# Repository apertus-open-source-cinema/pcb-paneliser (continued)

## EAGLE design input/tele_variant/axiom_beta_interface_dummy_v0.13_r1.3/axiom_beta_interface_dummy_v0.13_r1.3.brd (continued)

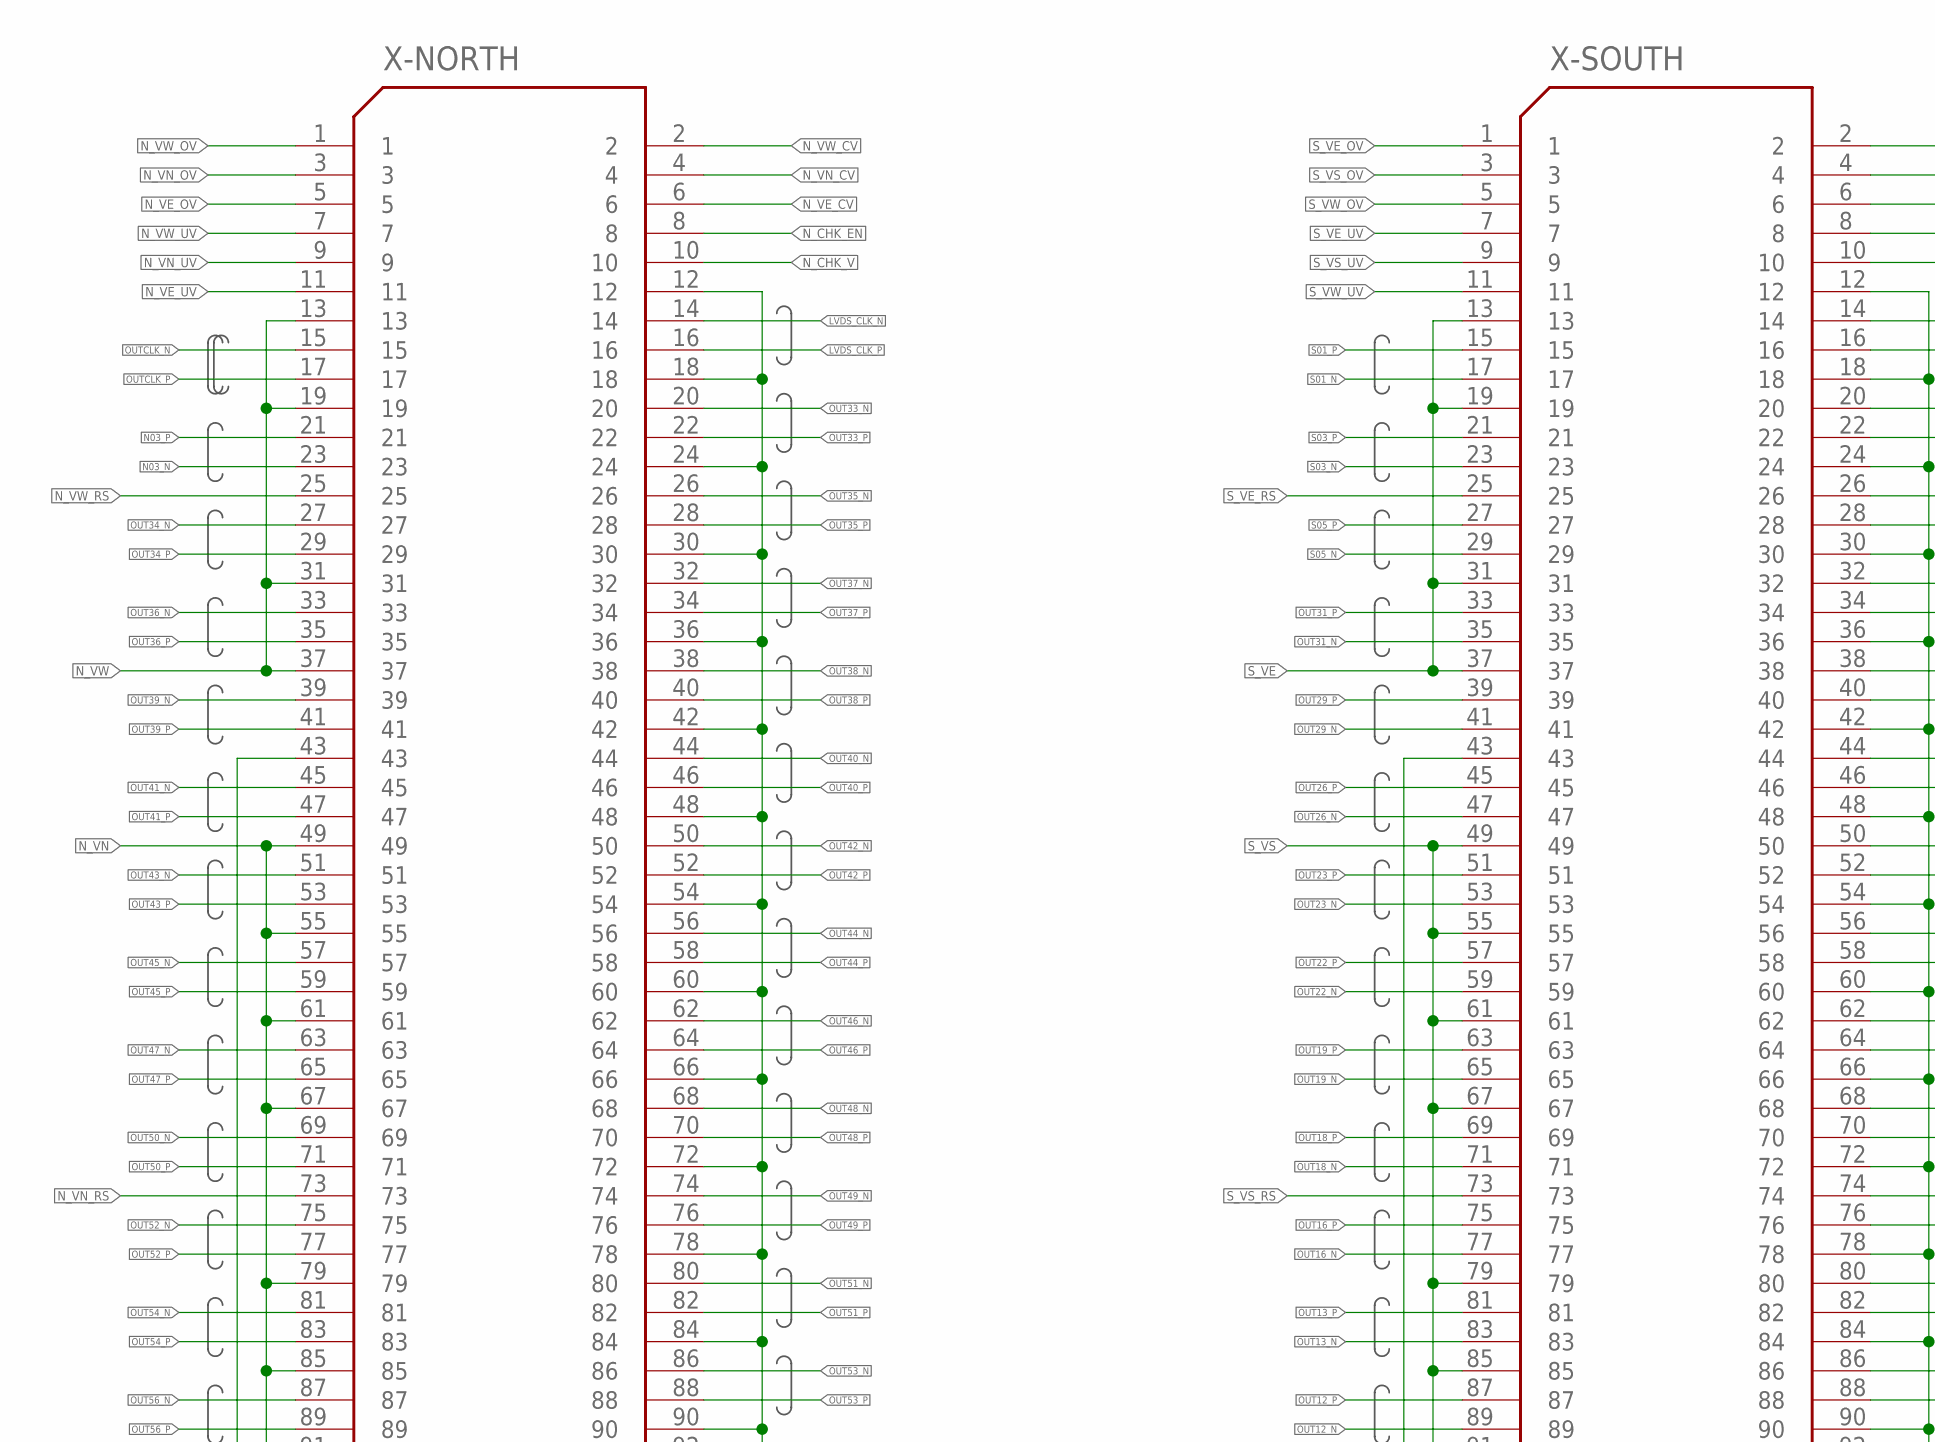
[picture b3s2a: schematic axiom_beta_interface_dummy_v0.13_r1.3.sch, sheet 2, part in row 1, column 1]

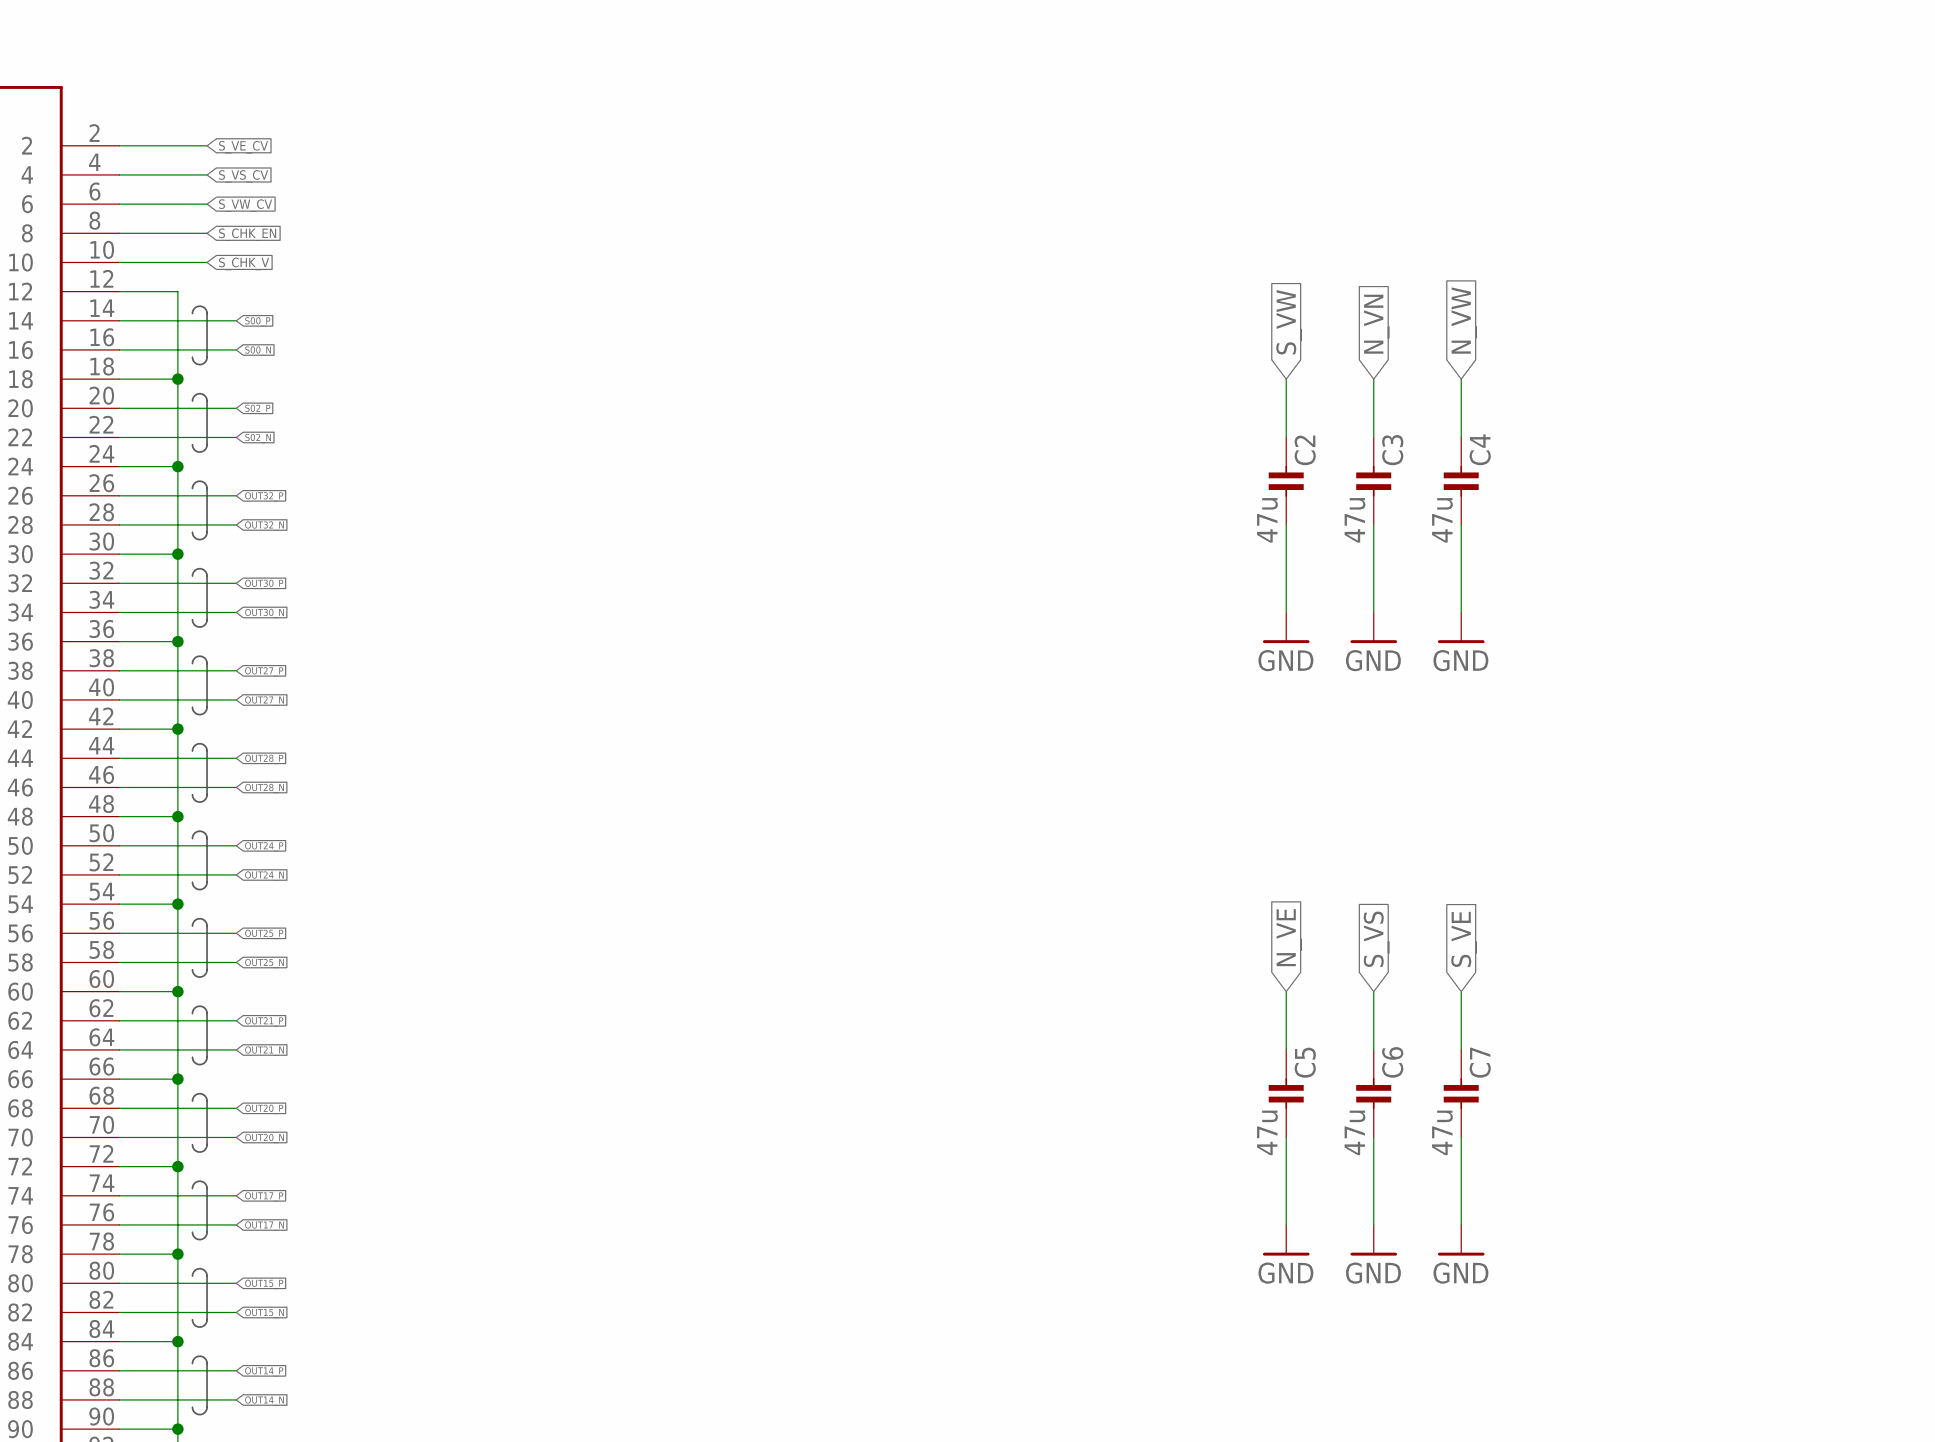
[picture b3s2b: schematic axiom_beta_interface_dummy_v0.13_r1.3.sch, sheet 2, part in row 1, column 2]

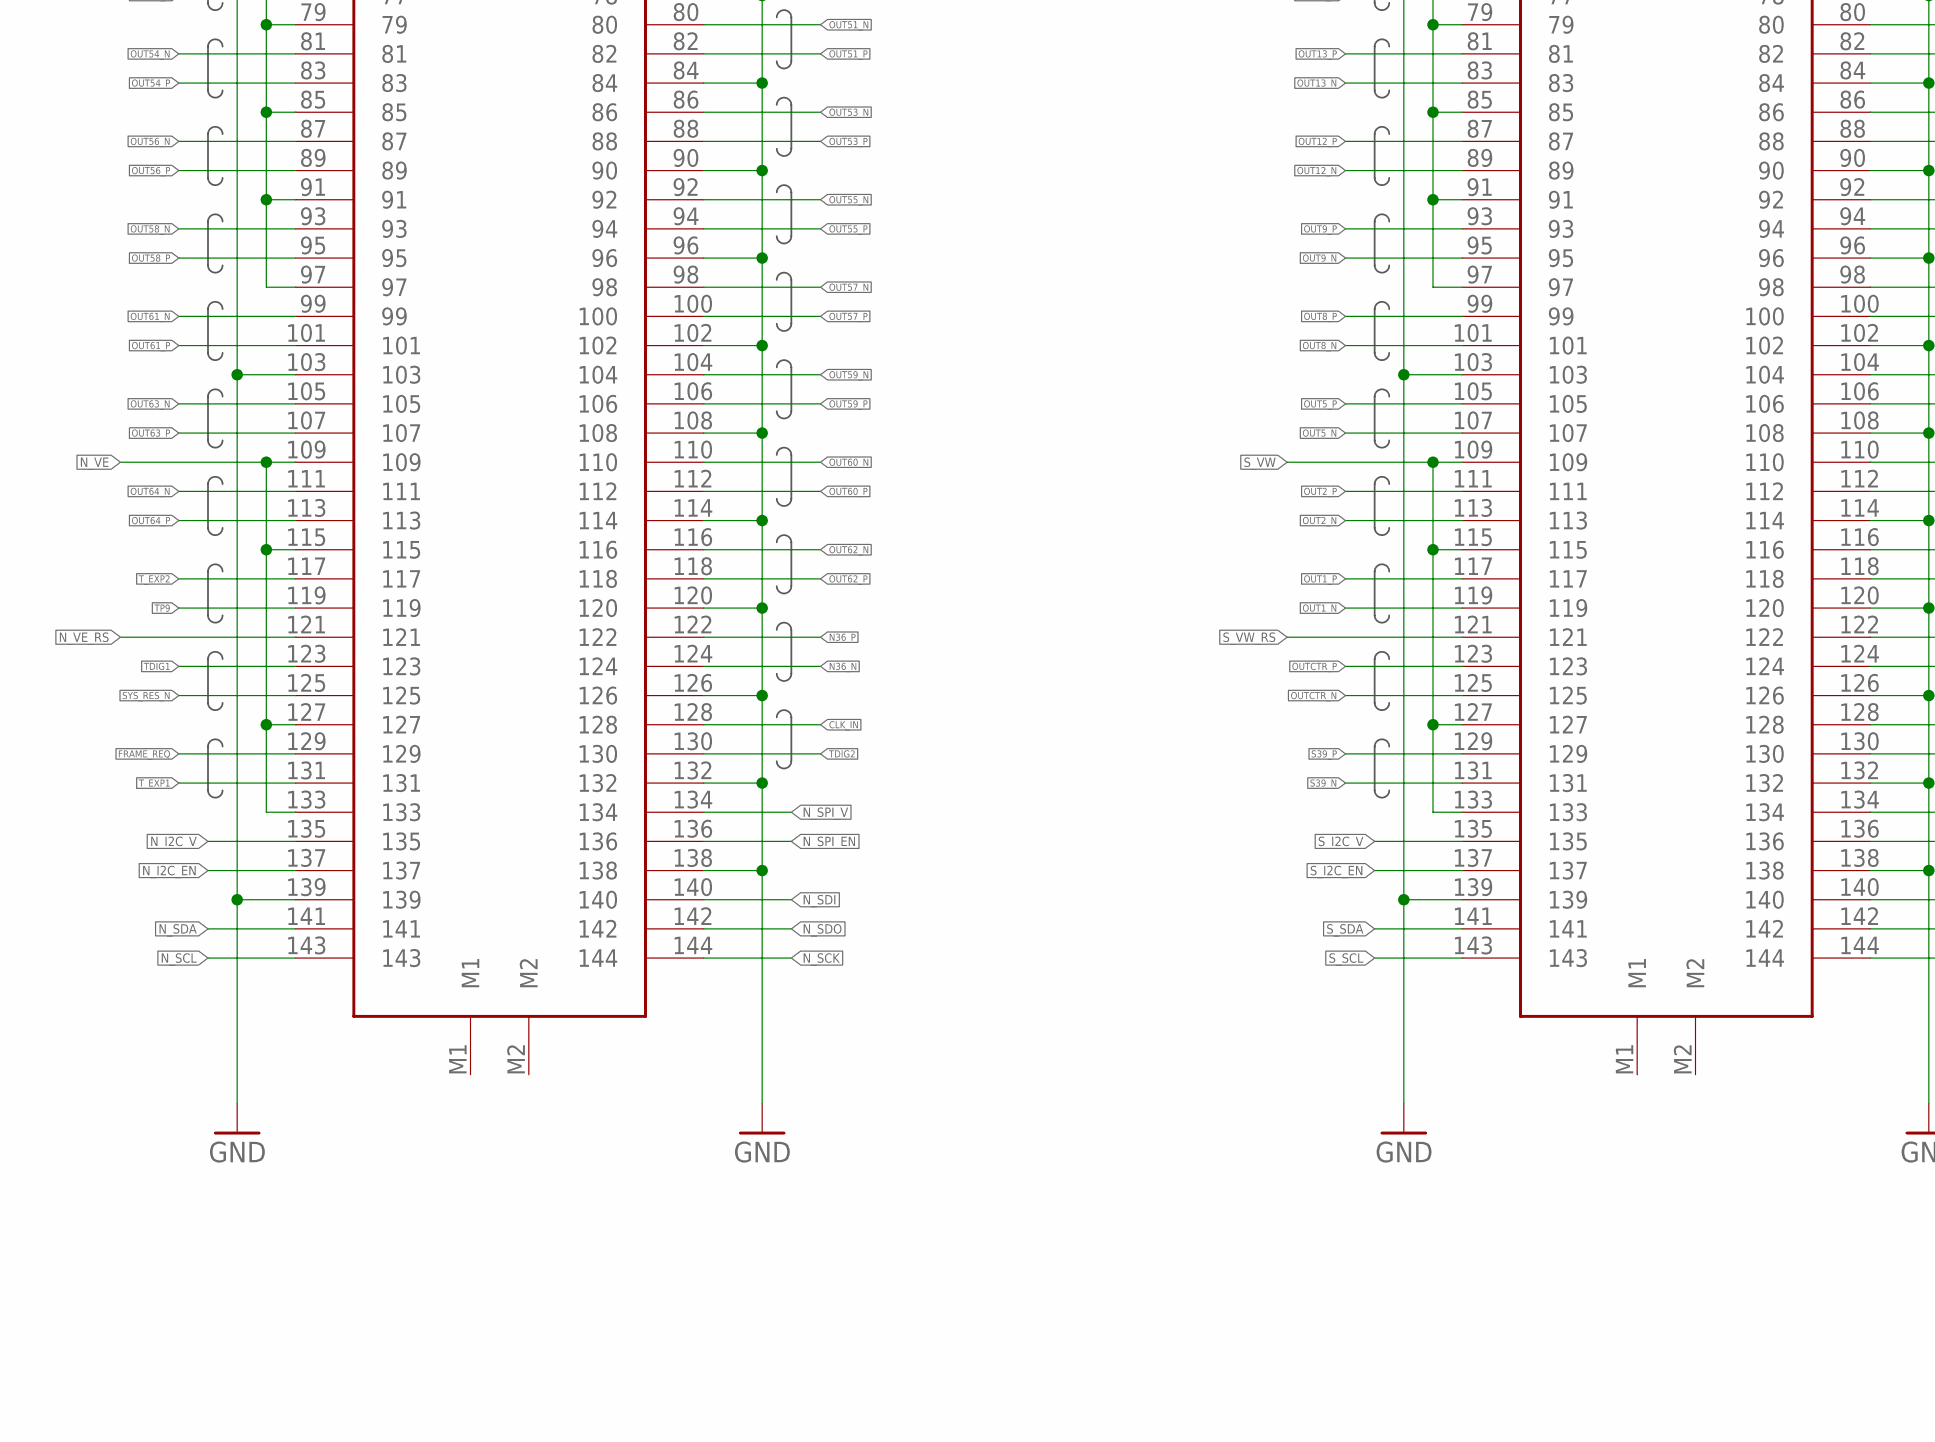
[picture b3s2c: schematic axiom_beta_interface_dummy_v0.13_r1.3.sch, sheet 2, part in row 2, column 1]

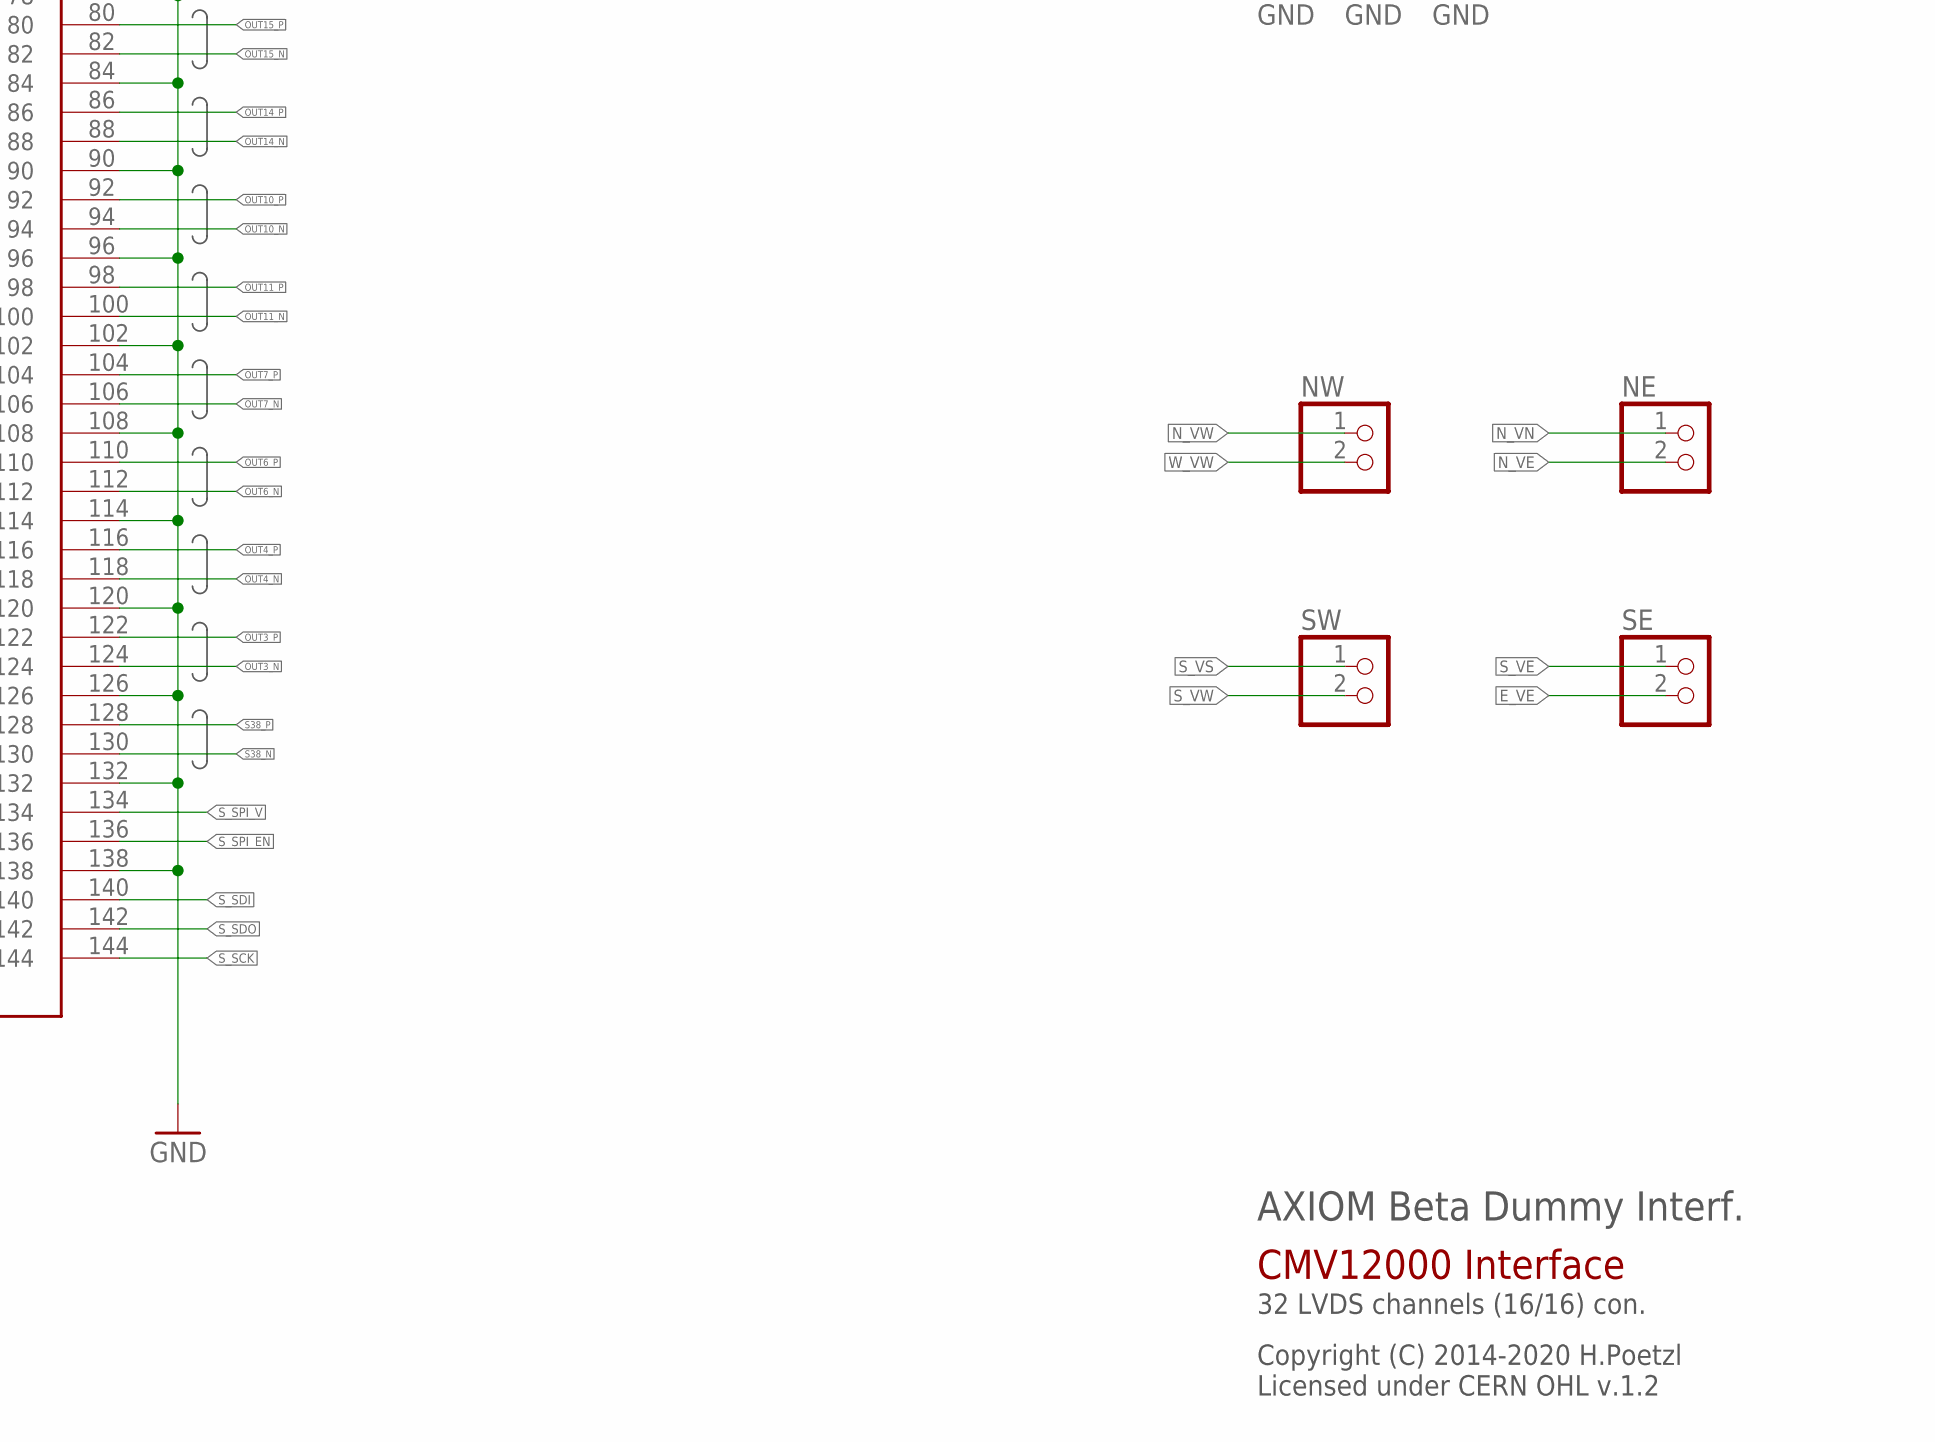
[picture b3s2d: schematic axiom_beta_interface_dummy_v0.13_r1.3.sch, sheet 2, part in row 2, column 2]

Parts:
C2, C3, C4, C5, C6, C7: 47u; 0805-B
NE: PINHD-1X02_2.54; 1X02
NW: PINHD-1X02_2.54; 1X02
SE: PINHD-1X02_2.54; 1X02
SW: PINHD-1X02_2.54; 1X02
X-NORTH: FX10-144S; FX10A-144S
X-SOUTH: FX10-144S; FX10A-144S

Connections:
CLK_IN: X-NORTH.128; also elsewhere on the board
E_VE: SE.2; also elsewhere on the board
FRAME_REQ: X-NORTH.129; also elsewhere on the board
GND: C2.2, C3.2, C4.2, C5.2, C6.2, C7.2, X-NORTH.12, X-NORTH.18, X-NORTH.24, X-NORTH.30, X-NORTH.36, X-NORTH.42, X-NORTH.43, X-NORTH.48, X-NORTH.54, X-NORTH.60, X-NORTH.66, X-NORTH.72, X-NORTH.78, X-NORTH.84, X-NORTH.90, X-NORTH.96, X-NORTH.102, X-NORTH.103, X-NORTH.108, X-NORTH.114, X-NORTH.120, X-NORTH.126, X-NORTH.132, X-NORTH.138, X-NORTH.139, X-SOUTH.12, X-SOUTH.18, X-SOUTH.24, X-SOUTH.30, X-SOUTH.36, X-SOUTH.42, X-SOUTH.43, X-SOUTH.48, X-SOUTH.54, X-SOUTH.60, X-SOUTH.66, X-SOUTH.72, X-SOUTH.78, X-SOUTH.84, X-SOUTH.90, X-SOUTH.96, X-SOUTH.102, X-SOUTH.103, X-SOUTH.108, X-SOUTH.114, X-SOUTH.120, X-SOUTH.126, X-SOUTH.132, X-SOUTH.138, X-SOUTH.139; also elsewhere on the board
LVDS_CLK_N: X-NORTH.14; also elsewhere on the board
LVDS_CLK_P: X-NORTH.16; also elsewhere on the board
N03_N: X-NORTH.23
N03_P: X-NORTH.21
N36_N: X-NORTH.124
N36_P: X-NORTH.122
N_CHK_EN: X-NORTH.8; also elsewhere on the board
N_CHK_V: X-NORTH.10; also elsewhere on the board
N_I2C_EN: X-NORTH.137; also elsewhere on the board
N_I2C_V: X-NORTH.135; also elsewhere on the board
N_SCK: X-NORTH.144; also elsewhere on the board
N_SCL: X-NORTH.143; also elsewhere on the board
N_SDA: X-NORTH.141; also elsewhere on the board
N_SDI: X-NORTH.140; also elsewhere on the board
N_SDO: X-NORTH.142; also elsewhere on the board
N_SPI_EN: X-NORTH.136; also elsewhere on the board
N_SPI_V: X-NORTH.134; also elsewhere on the board
N_VE: C5.1, NE.2, X-NORTH.109, X-NORTH.115, X-NORTH.127, X-NORTH.133
N_VE_CV: X-NORTH.6; also elsewhere on the board
N_VE_OV: X-NORTH.5; also elsewhere on the board
N_VE_RS: X-NORTH.121; also elsewhere on the board
N_VE_UV: X-NORTH.11; also elsewhere on the board
N_VN: C3.1, NE.1, X-NORTH.49, X-NORTH.55, X-NORTH.61, X-NORTH.67, X-NORTH.79, X-NORTH.85, X-NORTH.91, X-NORTH.97
N_VN_CV: X-NORTH.4; also elsewhere on the board
N_VN_OV: X-NORTH.3; also elsewhere on the board
N_VN_RS: X-NORTH.73; also elsewhere on the board
N_VN_UV: X-NORTH.9; also elsewhere on the board
N_VW: C4.1, NW.1, X-NORTH.13, X-NORTH.19, X-NORTH.31, X-NORTH.37
N_VW_CV: X-NORTH.2; also elsewhere on the board
N_VW_OV: X-NORTH.1; also elsewhere on the board
N_VW_RS: X-NORTH.25; also elsewhere on the board
N_VW_UV: X-NORTH.7; also elsewhere on the board
OUT1_N: X-SOUTH.119; also elsewhere on the board
OUT1_P: X-SOUTH.117; also elsewhere on the board
OUT2_N: X-SOUTH.113
OUT2_P: X-SOUTH.111
OUT3_N: X-SOUTH.124; also elsewhere on the board
OUT3_P: X-SOUTH.122; also elsewhere on the board
OUT4_N: X-SOUTH.118
OUT4_P: X-SOUTH.116
OUT5_N: X-SOUTH.107; also elsewhere on the board
OUT5_P: X-SOUTH.105; also elsewhere on the board
OUT6_N: X-SOUTH.112
OUT6_P: X-SOUTH.110
OUT7_N: X-SOUTH.106; also elsewhere on the board
OUT7_P: X-SOUTH.104; also elsewhere on the board
OUT8_N: X-SOUTH.101
OUT8_P: X-SOUTH.99
OUT9_N: X-SOUTH.95; also elsewhere on the board
OUT9_P: X-SOUTH.93; also elsewhere on the board
OUT10_N: X-SOUTH.94
OUT10_P: X-SOUTH.92
OUT11_N: X-SOUTH.100; also elsewhere on the board
OUT11_P: X-SOUTH.98; also elsewhere on the board
OUT12_N: X-SOUTH.89
OUT12_P: X-SOUTH.87
OUT13_N: X-SOUTH.83; also elsewhere on the board
OUT13_P: X-SOUTH.81; also elsewhere on the board
OUT14_N: X-SOUTH.88
OUT14_P: X-SOUTH.86
OUT15_N: X-SOUTH.82; also elsewhere on the board
OUT15_P: X-SOUTH.80; also elsewhere on the board
OUT16_N: X-SOUTH.77
OUT16_P: X-SOUTH.75
OUT17_N: X-SOUTH.76; also elsewhere on the board
OUT17_P: X-SOUTH.74; also elsewhere on the board
OUT18_N: X-SOUTH.71
OUT18_P: X-SOUTH.69
OUT19_N: X-SOUTH.65; also elsewhere on the board
OUT19_P: X-SOUTH.63; also elsewhere on the board
OUT20_N: X-SOUTH.70
OUT20_P: X-SOUTH.68
OUT21_N: X-SOUTH.64; also elsewhere on the board
OUT21_P: X-SOUTH.62; also elsewhere on the board
OUT22_N: X-SOUTH.59
OUT22_P: X-SOUTH.57
OUT23_N: X-SOUTH.53; also elsewhere on the board
OUT23_P: X-SOUTH.51; also elsewhere on the board
OUT24_N: X-SOUTH.52
OUT24_P: X-SOUTH.50
OUT25_N: X-SOUTH.58; also elsewhere on the board
OUT25_P: X-SOUTH.56; also elsewhere on the board
OUT26_N: X-SOUTH.47
OUT26_P: X-SOUTH.45
OUT27_N: X-SOUTH.40; also elsewhere on the board
OUT27_P: X-SOUTH.38; also elsewhere on the board
OUT28_N: X-SOUTH.46
OUT28_P: X-SOUTH.44
OUT29_N: X-SOUTH.41; also elsewhere on the board
OUT29_P: X-SOUTH.39; also elsewhere on the board
OUT30_N: X-SOUTH.34
OUT30_P: X-SOUTH.32
OUT31_N: X-SOUTH.35; also elsewhere on the board
OUT31_P: X-SOUTH.33; also elsewhere on the board
OUT32_N: X-SOUTH.28
OUT32_P: X-SOUTH.26
OUT33_N: X-NORTH.20; also elsewhere on the board
OUT33_P: X-NORTH.22; also elsewhere on the board
OUT34_N: X-NORTH.27
OUT34_P: X-NORTH.29
OUT35_N: X-NORTH.26; also elsewhere on the board
OUT35_P: X-NORTH.28; also elsewhere on the board
OUT36_N: X-NORTH.33
OUT36_P: X-NORTH.35
OUT37_N: X-NORTH.32; also elsewhere on the board
OUT37_P: X-NORTH.34; also elsewhere on the board
OUT38_N: X-NORTH.38
OUT38_P: X-NORTH.40
OUT39_N: X-NORTH.39; also elsewhere on the board
OUT39_P: X-NORTH.41; also elsewhere on the board
OUT40_N: X-NORTH.44
OUT40_P: X-NORTH.46
OUT41_N: X-NORTH.45; also elsewhere on the board
OUT41_P: X-NORTH.47; also elsewhere on the board
OUT42_N: X-NORTH.50
OUT42_P: X-NORTH.52
OUT43_N: X-NORTH.51; also elsewhere on the board
OUT43_P: X-NORTH.53; also elsewhere on the board
OUT44_N: X-NORTH.56
OUT44_P: X-NORTH.58
OUT45_N: X-NORTH.57; also elsewhere on the board
OUT45_P: X-NORTH.59; also elsewhere on the board
OUT46_N: X-NORTH.62
OUT46_P: X-NORTH.64
OUT47_N: X-NORTH.63; also elsewhere on the board
OUT47_P: X-NORTH.65; also elsewhere on the board
OUT48_N: X-NORTH.68
OUT48_P: X-NORTH.70
OUT49_N: X-NORTH.74; also elsewhere on the board
OUT49_P: X-NORTH.76; also elsewhere on the board
OUT50_N: X-NORTH.69
OUT50_P: X-NORTH.71
OUT51_N: X-NORTH.80; also elsewhere on the board
OUT51_P: X-NORTH.82; also elsewhere on the board
OUT52_N: X-NORTH.75
OUT52_P: X-NORTH.77
OUT53_N: X-NORTH.86; also elsewhere on the board
OUT53_P: X-NORTH.88; also elsewhere on the board
OUT54_N: X-NORTH.81
OUT54_P: X-NORTH.83
OUT55_N: X-NORTH.92; also elsewhere on the board
OUT55_P: X-NORTH.94; also elsewhere on the board
OUT56_N: X-NORTH.87
OUT56_P: X-NORTH.89
OUT57_N: X-NORTH.98; also elsewhere on the board
OUT57_P: X-NORTH.100; also elsewhere on the board
OUT58_N: X-NORTH.93
OUT58_P: X-NORTH.95
OUT59_N: X-NORTH.104; also elsewhere on the board
OUT59_P: X-NORTH.106; also elsewhere on the board
OUT60_N: X-NORTH.110
OUT60_P: X-NORTH.112
OUT61_N: X-NORTH.99; also elsewhere on the board
OUT61_P: X-NORTH.101; also elsewhere on the board
OUT62_N: X-NORTH.116
OUT62_P: X-NORTH.118
OUT63_N: X-NORTH.105; also elsewhere on the board
OUT63_P: X-NORTH.107; also elsewhere on the board
OUT64_N: X-NORTH.111
OUT64_P: X-NORTH.113
OUTCLK_N: X-NORTH.15; also elsewhere on the board
OUTCLK_P: X-NORTH.17; also elsewhere on the board
OUTCTR_N: X-SOUTH.125; also elsewhere on the board
OUTCTR_P: X-SOUTH.123; also elsewhere on the board
S00_N: X-SOUTH.16
S00_P: X-SOUTH.14
S01_N: X-SOUTH.17
S01_P: X-SOUTH.15
S02_N: X-SOUTH.22
S02_P: X-SOUTH.20
S03_N: X-SOUTH.23
S03_P: X-SOUTH.21
S05_N: X-SOUTH.29
S05_P: X-SOUTH.27
S38_N: X-SOUTH.130
S38_P: X-SOUTH.128
S39_N: X-SOUTH.131
S39_P: X-SOUTH.129
SYS_RES_N: X-NORTH.125; also elsewhere on the board
S_CHK_EN: X-SOUTH.8; also elsewhere on the board
S_CHK_V: X-SOUTH.10; also elsewhere on the board
S_I2C_EN: X-SOUTH.137; also elsewhere on the board
S_I2C_V: X-SOUTH.135; also elsewhere on the board
S_SCK: X-SOUTH.144; also elsewhere on the board
S_SCL: X-SOUTH.143; also elsewhere on the board
S_SDA: X-SOUTH.141; also elsewhere on the board
S_SDI: X-SOUTH.140; also elsewhere on the board
S_SDO: X-SOUTH.142; also elsewhere on the board
S_SPI_EN: X-SOUTH.136; also elsewhere on the board
S_SPI_V: X-SOUTH.134; also elsewhere on the board
S_VE: C7.1, SE.1, X-SOUTH.13, X-SOUTH.19, X-SOUTH.31, X-SOUTH.37
S_VE_CV: X-SOUTH.2; also elsewhere on the board
S_VE_OV: X-SOUTH.1; also elsewhere on the board
S_VE_RS: X-SOUTH.25; also elsewhere on the board
S_VE_UV: X-SOUTH.7; also elsewhere on the board
S_VS: C6.1, SW.1, X-SOUTH.49, X-SOUTH.55, X-SOUTH.61, X-SOUTH.67, X-SOUTH.79, X-SOUTH.85, X-SOUTH.91, X-SOUTH.97
S_VS_CV: X-SOUTH.4; also elsewhere on the board
S_VS_OV: X-SOUTH.3; also elsewhere on the board
S_VS_RS: X-SOUTH.73; also elsewhere on the board
S_VS_UV: X-SOUTH.9; also elsewhere on the board
S_VW: C2.1, SW.2, X-SOUTH.109, X-SOUTH.115, X-SOUTH.127, X-SOUTH.133
S_VW_CV: X-SOUTH.6; also elsewhere on the board
S_VW_OV: X-SOUTH.5; also elsewhere on the board
S_VW_RS: X-SOUTH.121; also elsewhere on the board
S_VW_UV: X-SOUTH.11; also elsewhere on the board
TDIG1: X-NORTH.123; also elsewhere on the board
TDIG2: X-NORTH.130
TP9: X-NORTH.119
T_EXP1: X-NORTH.131; also elsewhere on the board
T_EXP2: X-NORTH.117; also elsewhere on the board
W_VW: NW.2; also elsewhere on the board

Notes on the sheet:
AXIOM Beta Dummy Interf.
Copyright (C) 2014-2020 H.Poetzl Licensed under CERN OHL v.1.2
CMV12000 Interface
32 LVDS channels (16/16) con.

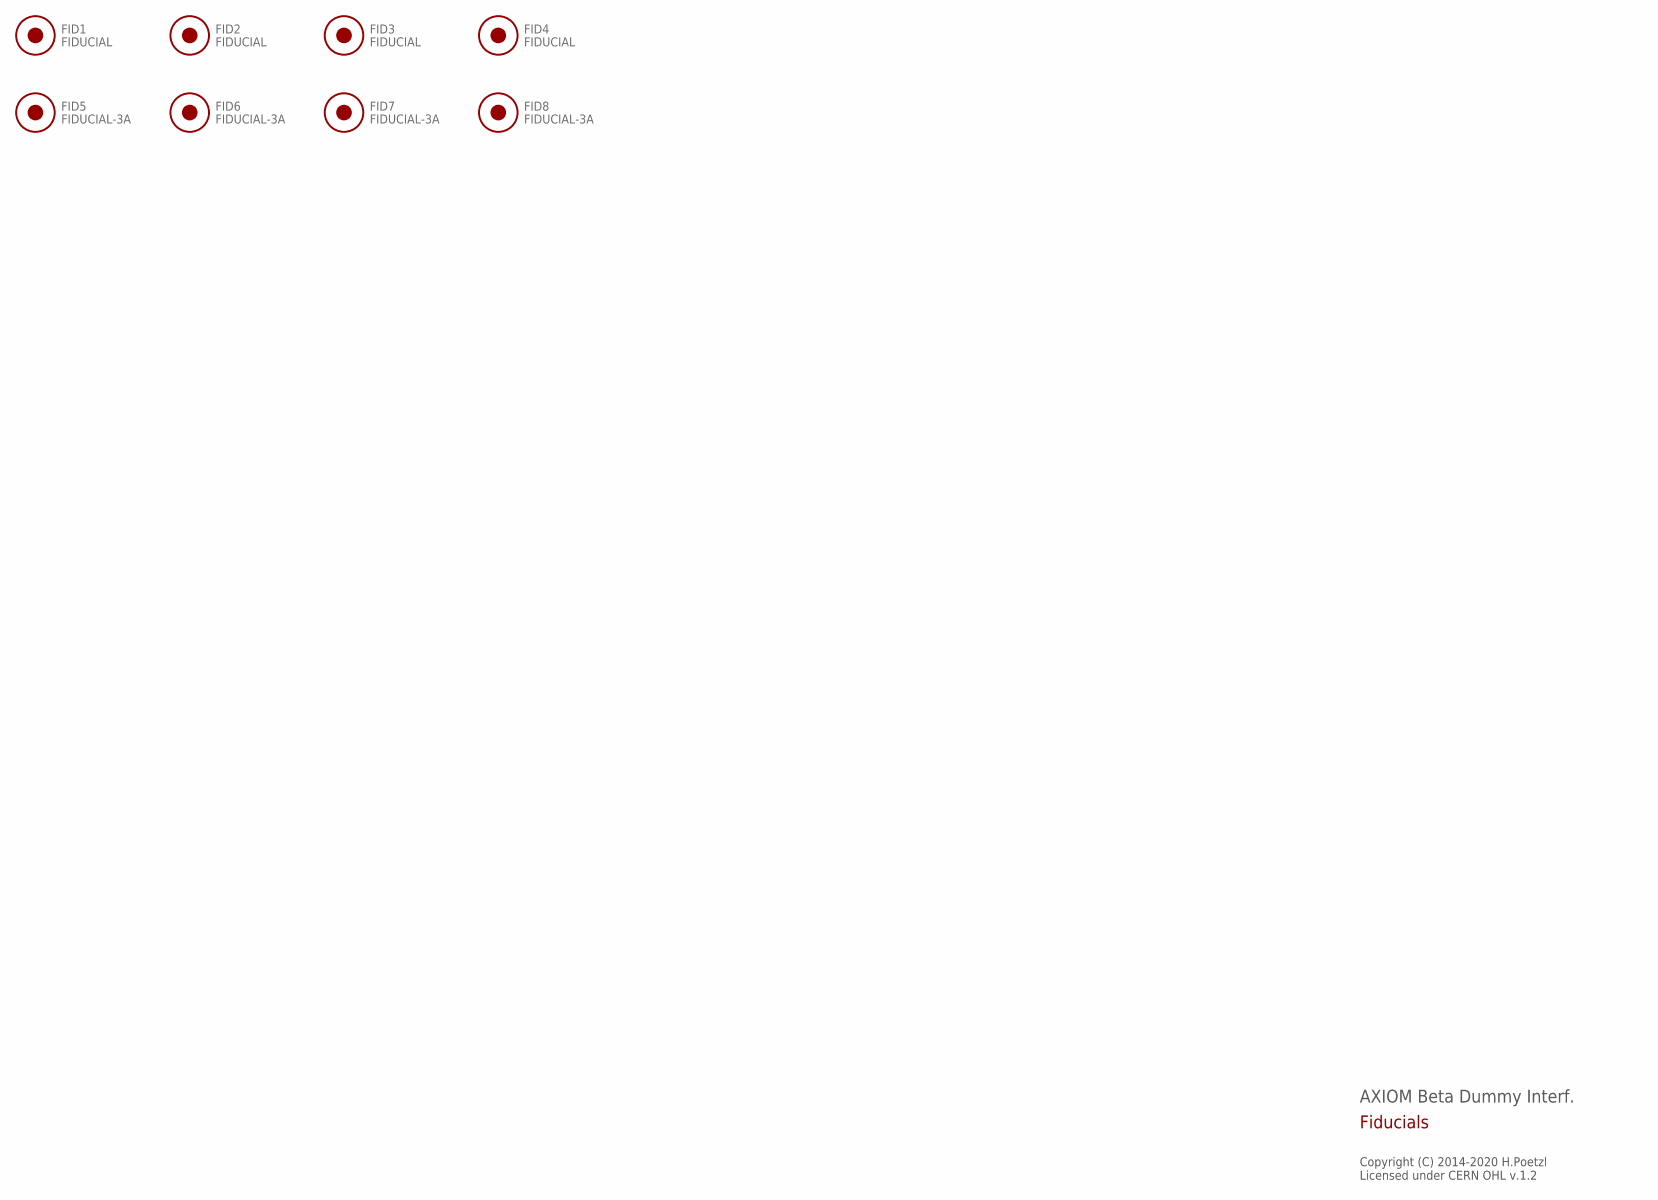
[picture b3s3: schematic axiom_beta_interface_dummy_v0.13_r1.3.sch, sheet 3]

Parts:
FID1, FID2, FID3, FID4: FIDUCIAL; FID_ARROW
FID5, FID6, FID7, FID8: FIDUCIAL-3A; FID_3ARROW

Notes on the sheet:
AXIOM Beta Dummy Interf.
Copyright (C) 2014-2020 H.Poetzl Licensed under CERN OHL v.1.2
Fiducials

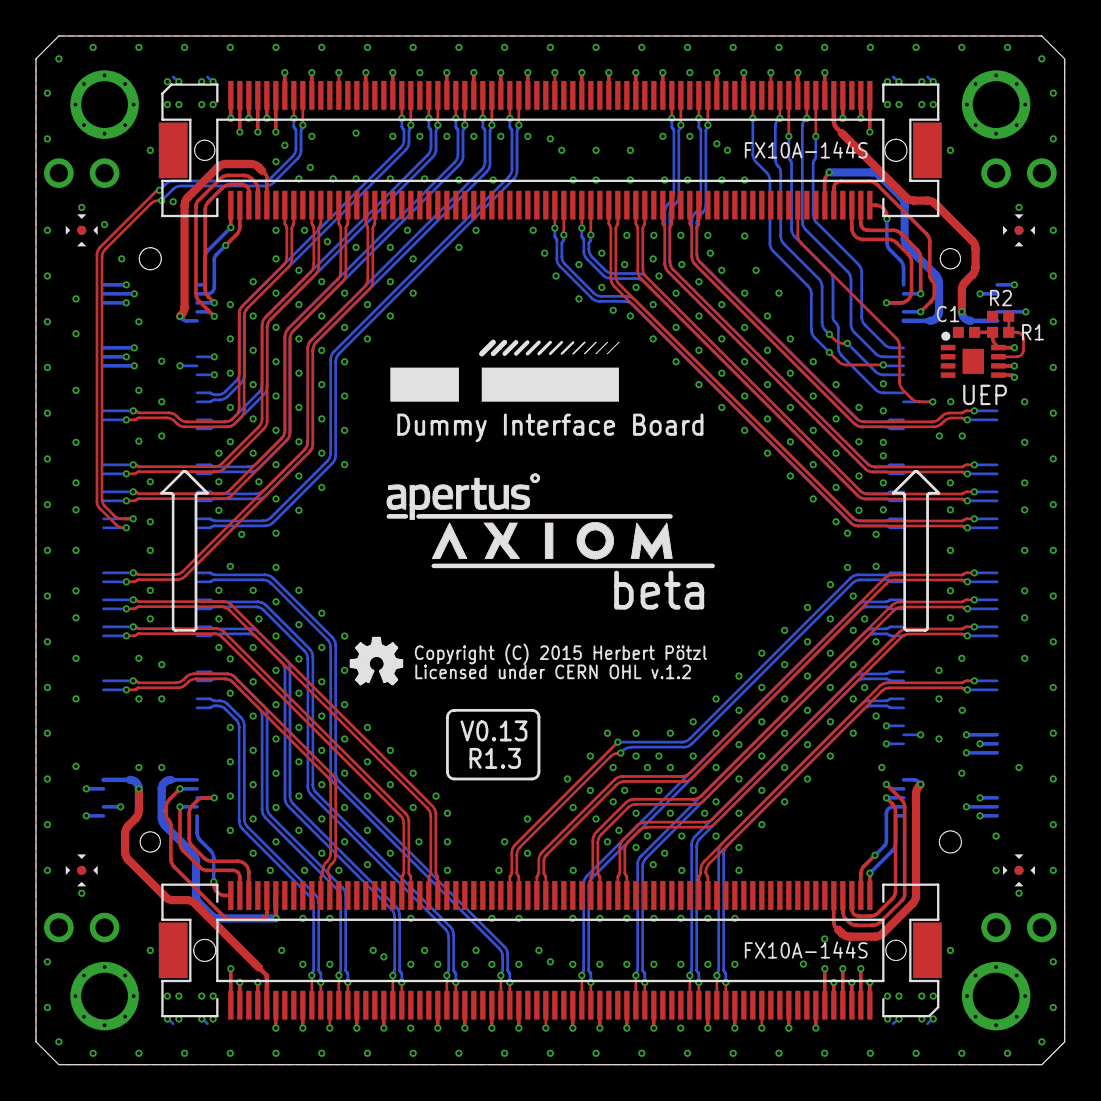
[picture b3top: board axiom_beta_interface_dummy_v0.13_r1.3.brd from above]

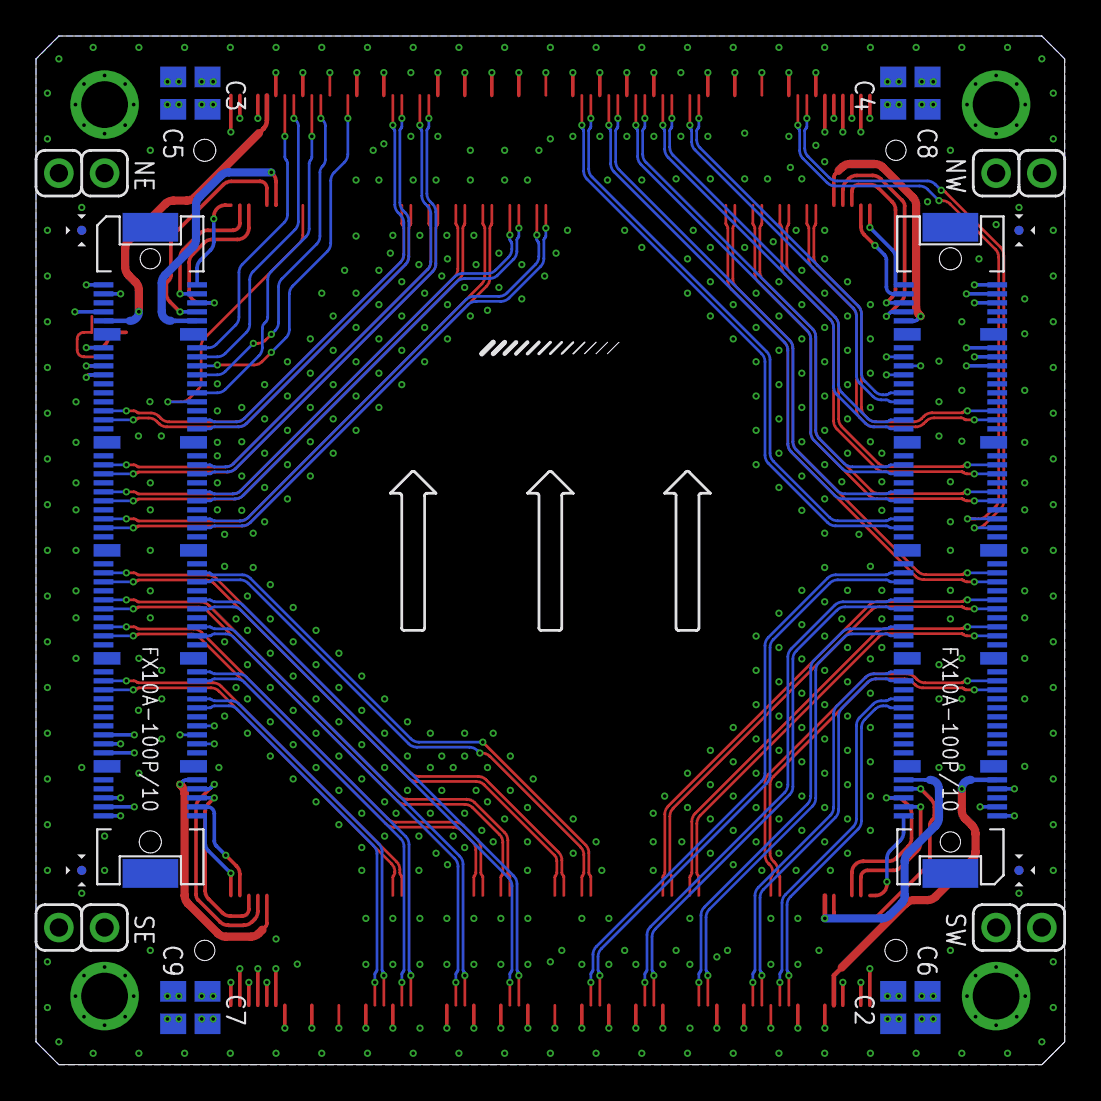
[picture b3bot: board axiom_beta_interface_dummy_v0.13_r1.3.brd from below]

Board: 4 copper layers, 57.1 x 57.1 mm, 33 parts (18 on the bottom side), 135 nets.

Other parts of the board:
LOGO1: OSHW_LOGO_FILLX0100-NT; OSHW_FILLX100_NOTEXT
PARALLELLA: PARALLELLA-FRAME
U$1: µZ-FRAME
U$2: APERTUS_LOGO334X100; APERTUS_LOGO_334X100
U$3: AXIOM_LOGO525X80; AXIOM_LOGO_525X80
